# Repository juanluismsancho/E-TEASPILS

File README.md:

# E-TEASPILS
Teaching Environmental Awareness with Smart IoT Planters in Learning Spaces (TEASPILS)
Versión desarrollada por Juan Arquero, dentro del proyecto TEASPILS, Universidad Politécnica de Madrid

#TEASPIKE
Teaspike is a technological teaching tool that seechs to introduce students into IoT technoloy giving them the capability of monitoring planters installed in educational spaces.

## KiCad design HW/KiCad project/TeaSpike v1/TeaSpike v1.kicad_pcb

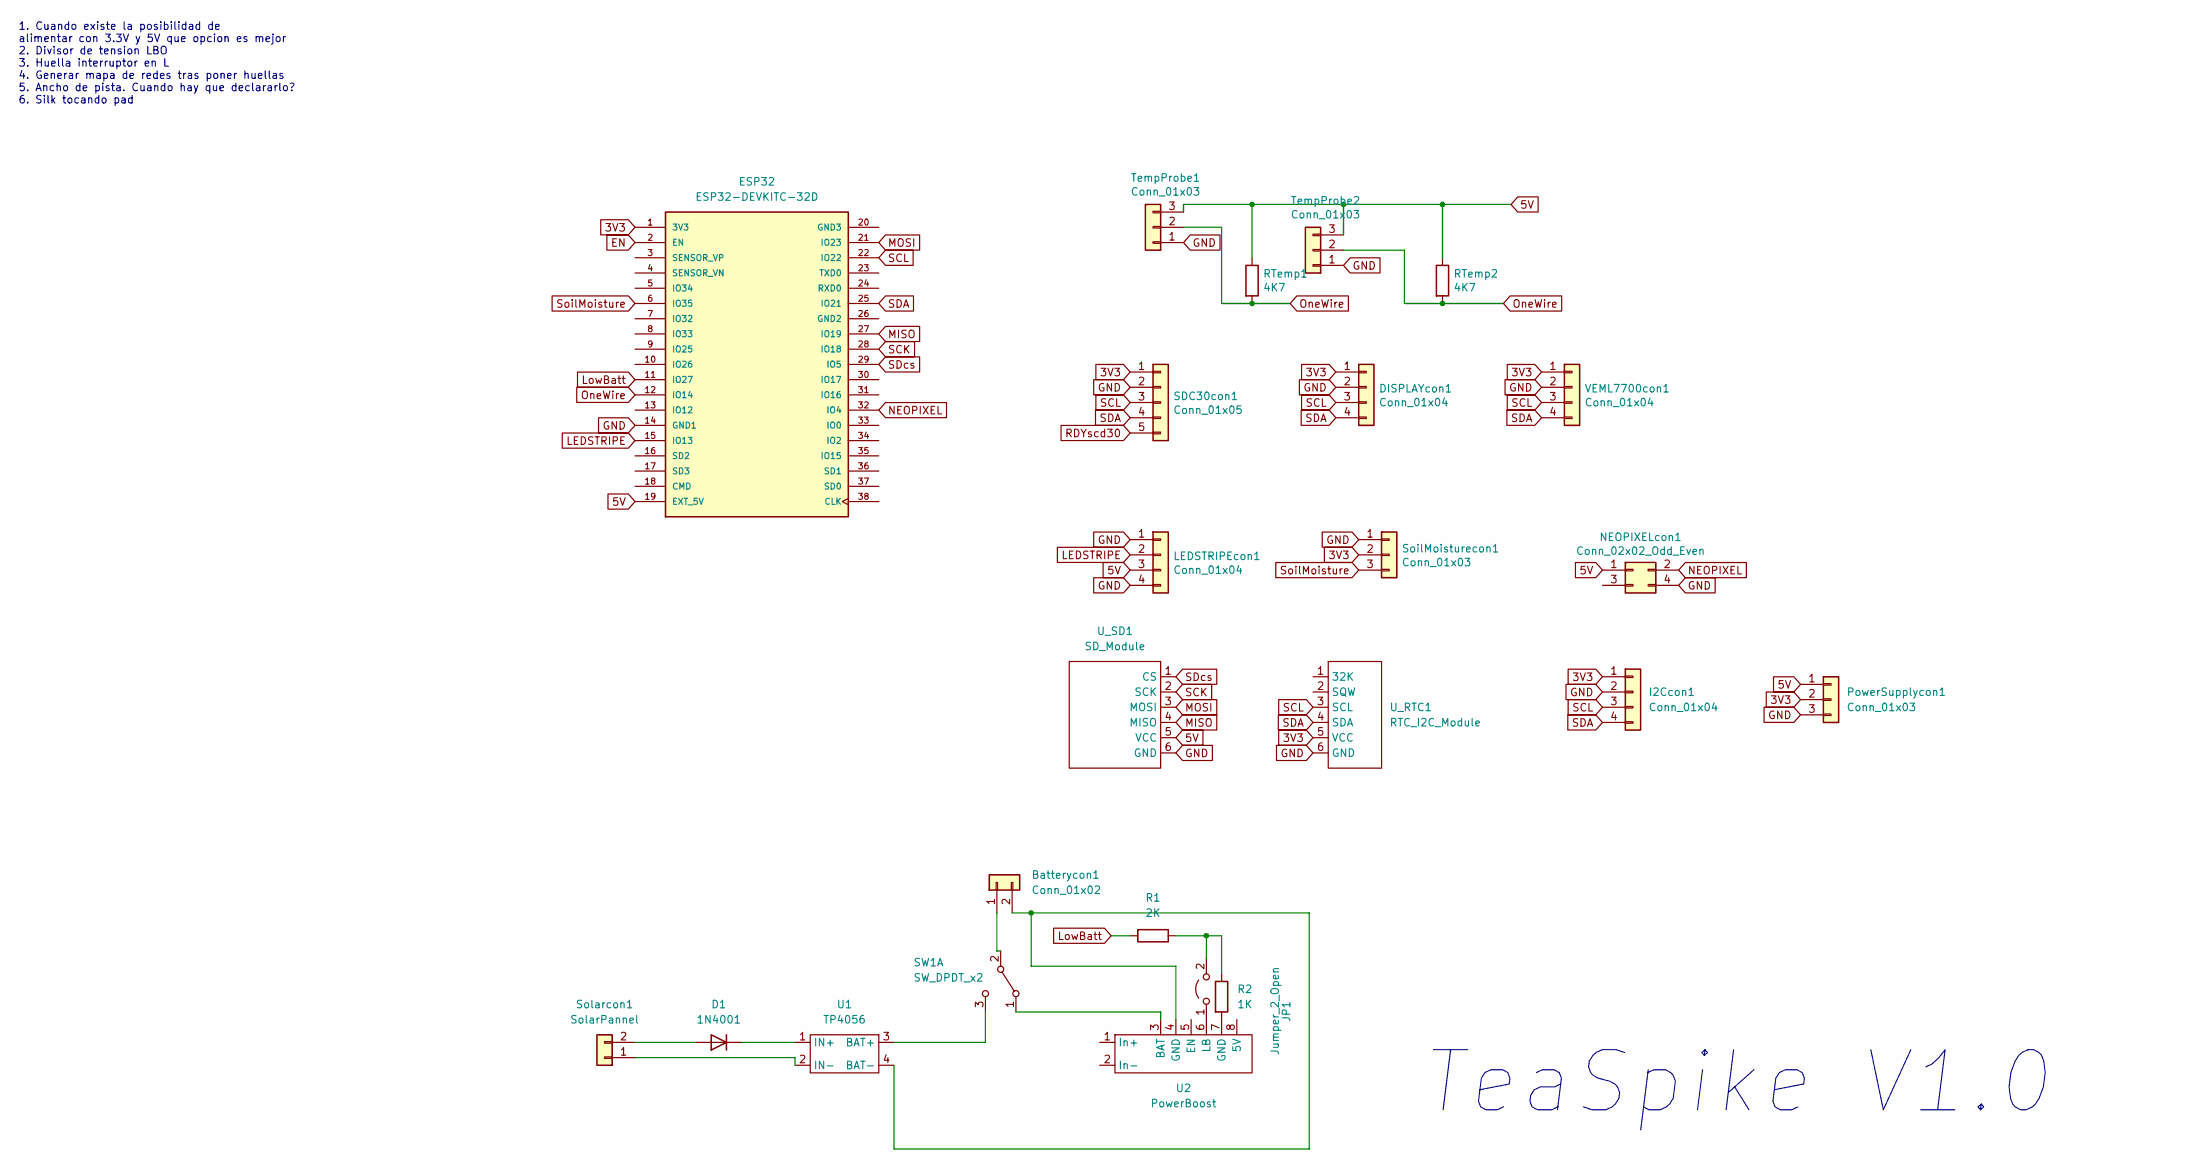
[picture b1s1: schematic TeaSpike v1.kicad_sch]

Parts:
Batterycon1: Conn_01x02; TerminalBlock_bornier-2_P5.08mm
D1: 1N4001; D_DO-41_SOD81_P10.16mm_Horizontal
DISPLAYcon1: Conn_01x04; JST_EH_B4B-EH-A_1x04_P2.50mm_Vertical
ESP32: ESP32-DEVKITC-32D; MODULE_ESP32-DEVKITC-32D; PARTREV 4
I2Ccon1: Conn_01x04; PinSocket_1x04_P2.54mm_Vertical
JP1: Jumper_2_Open; PinHeader_1x02_P2.54mm_Vertical
LEDSTRIPEcon1: Conn_01x04; JST_EH_B4B-EH-A_1x04_P2.50mm_Vertical
NEOPIXELcon1: Conn_02x02_Odd_Even; PinSocket_2x02_P2.54mm_Vertical
PowerSupplycon1: Conn_01x03; PinSocket_1x03_P2.54mm_Vertical
R1: 2K; R_Axial_DIN0207_L6.3mm_D2.5mm_P7.62mm_Horizontal
R2: 1K; R_Axial_DIN0207_L6.3mm_D2.5mm_P7.62mm_Horizontal
RTemp1, RTemp2: 4K7; R_Axial_DIN0207_L6.3mm_D2.5mm_P7.62mm_Horizontal
SDC30con1: Conn_01x05; JST_EH_B5B-EH-A_1x05_P2.50mm_Vertical
SW1: SW_DPDT_x2; SW_CuK_JS202011AQN_DPDT_Angled
SoilMoisturecon1: Conn_01x03; PinHeader_1x03_P2.54mm_Vertical
Solarcon1: SolarPannel; TerminalBlock_bornier-2_P5.08mm
TempProbe1, TempProbe2: Conn_01x03; JST_EH_B3B-EH-A_1x03_P2.50mm_Vertical
U1: TP4056
U2: PowerBoost
U_RTC1: RTC_I2C_Module
U_SD1: SD_Module
VEML7700con1: Conn_01x04; JST_EH_B4B-EH-A_1x04_P2.50mm_Vertical

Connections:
3V3: DISPLAYcon1.1, ESP32.1 (3V3), I2Ccon1.1, PowerSupplycon1.2, SDC30con1.1, SoilMoisturecon1.2, U_RTC1.5 (VCC), VEML7700con1.1
5V: ESP32.19 (EXT_5V), LEDSTRIPEcon1.3, NEOPIXELcon1.1, PowerSupplycon1.1, RTemp1.1, RTemp2.1, TempProbe1.3, TempProbe2.3, U_SD1.5 (VCC)
EN: ESP32.2 (EN)
GND: DISPLAYcon1.2, ESP32.14 (GND1), I2Ccon1.2, LEDSTRIPEcon1.1, LEDSTRIPEcon1.4, NEOPIXELcon1.4, PowerSupplycon1.3, SDC30con1.2, SoilMoisturecon1.1, TempProbe1.1, TempProbe2.1, U_RTC1.6 (GND), U_SD1.6 (GND), VEML7700con1.2
LEDSTRIPE: ESP32.15 (IO13), LEDSTRIPEcon1.2
LowBatt: ESP32.11 (IO27), R1.2
MISO: ESP32.27 (IO19), U_SD1.4 (MISO)
MOSI: ESP32.21 (IO23), U_SD1.3 (MOSI)
NEOPIXEL: ESP32.32 (IO4), NEOPIXELcon1.2
unnamed 9: Batterycon1.1, SW1.2 (B); also elsewhere on the board
unnamed: Batterycon1.2, U1.4 (BAT-), U2.4 (GND)
unnamed: D1.1 (K), U1.1 (IN+)
unnamed: D1.2 (A), Solarcon1.2
unnamed: JP1.1 (A), U2.6 (LB)
unnamed: JP1.2 (B), R1.1, R2.1
unnamed: R2.2, U2.7 (GND)
unnamed 16: SW1.1 (A), U2.3 (BAT); also elsewhere on the board
unnamed 17: SW1.3 (C), U1.3 (BAT+); also elsewhere on the board
unnamed: Solarcon1.1, U1.2 (IN-)
OneWire: ESP32.12 (IO14), RTemp1.2, RTemp2.2, TempProbe1.2, TempProbe2.2
RDYscd30: SDC30con1.5
SCK: ESP32.28 (IO18), U_SD1.2 (SCK)
SCL: DISPLAYcon1.3, ESP32.22 (IO22), I2Ccon1.3, SDC30con1.3, U_RTC1.3 (SCL), VEML7700con1.3
SDA: DISPLAYcon1.4, ESP32.25 (IO21), I2Ccon1.4, SDC30con1.4, U_RTC1.4 (SDA), VEML7700con1.4
SDcs: ESP32.29 (IO5), U_SD1.1 (CS)
SoilMoisture: ESP32.6 (IO35), SoilMoisturecon1.3

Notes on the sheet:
TeaSpike V1.0
1. Cuando existe la posibilidad de alimentar con 3.3V y 5V que opcion es mejor 2. Divisor de tension LBO 3. Huella interruptor en L 4. Generar mapa de redes tras poner huellas 5. Ancho de pista. Cuando hay que declararlo? 6. Silk tocando pad

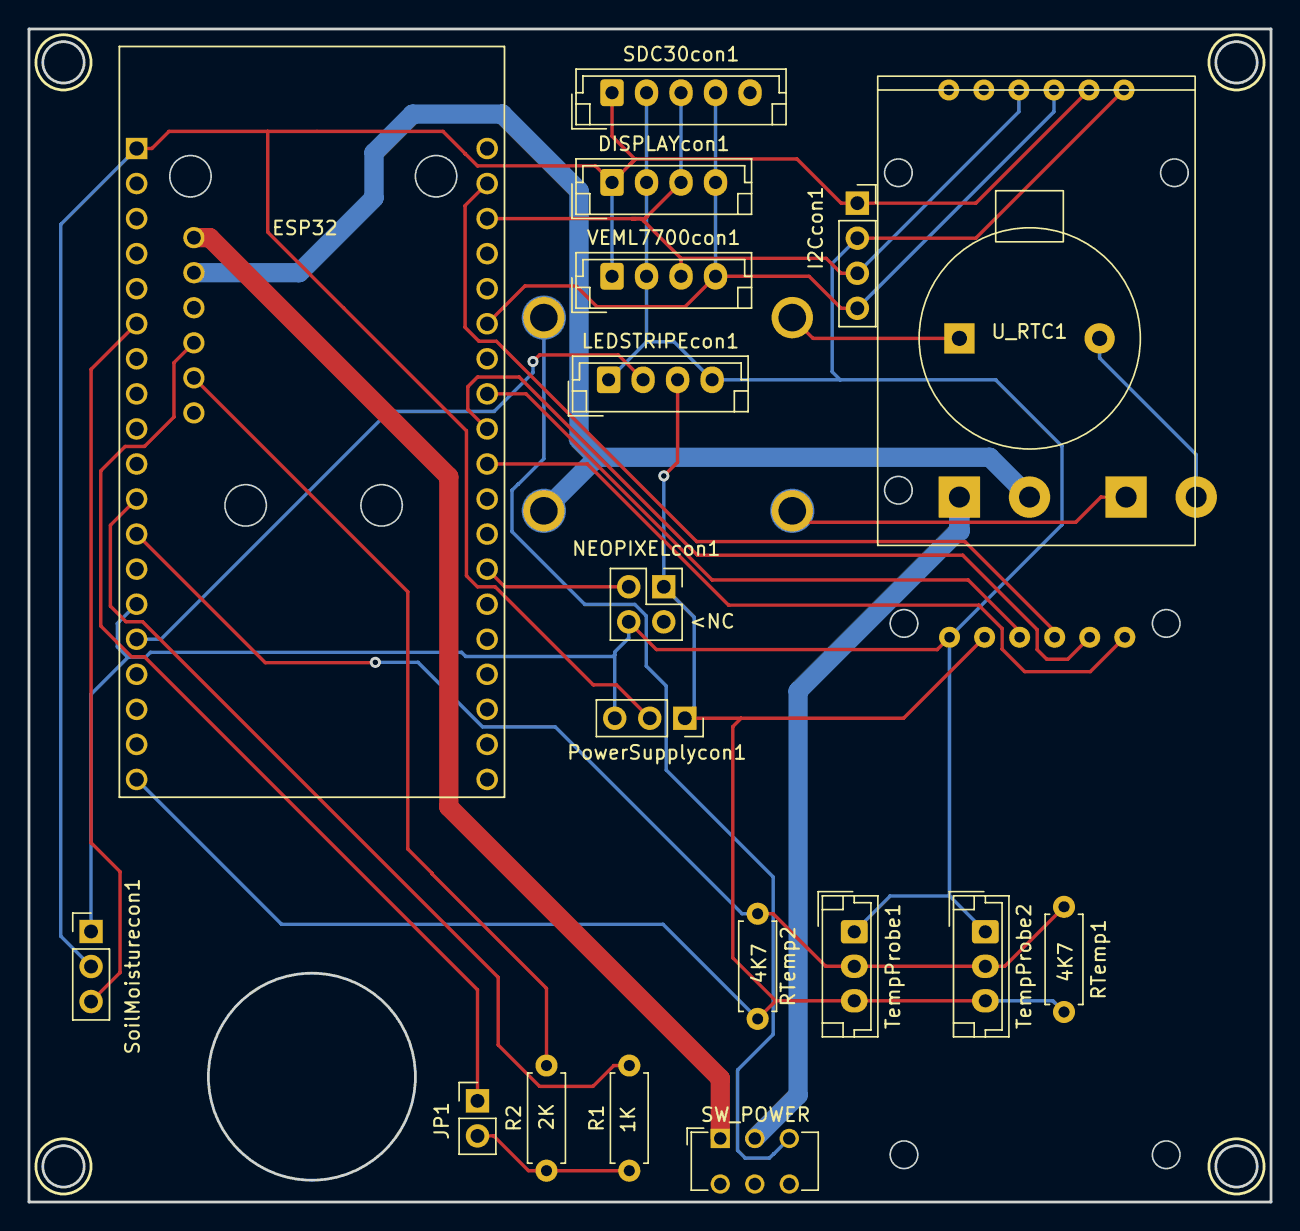
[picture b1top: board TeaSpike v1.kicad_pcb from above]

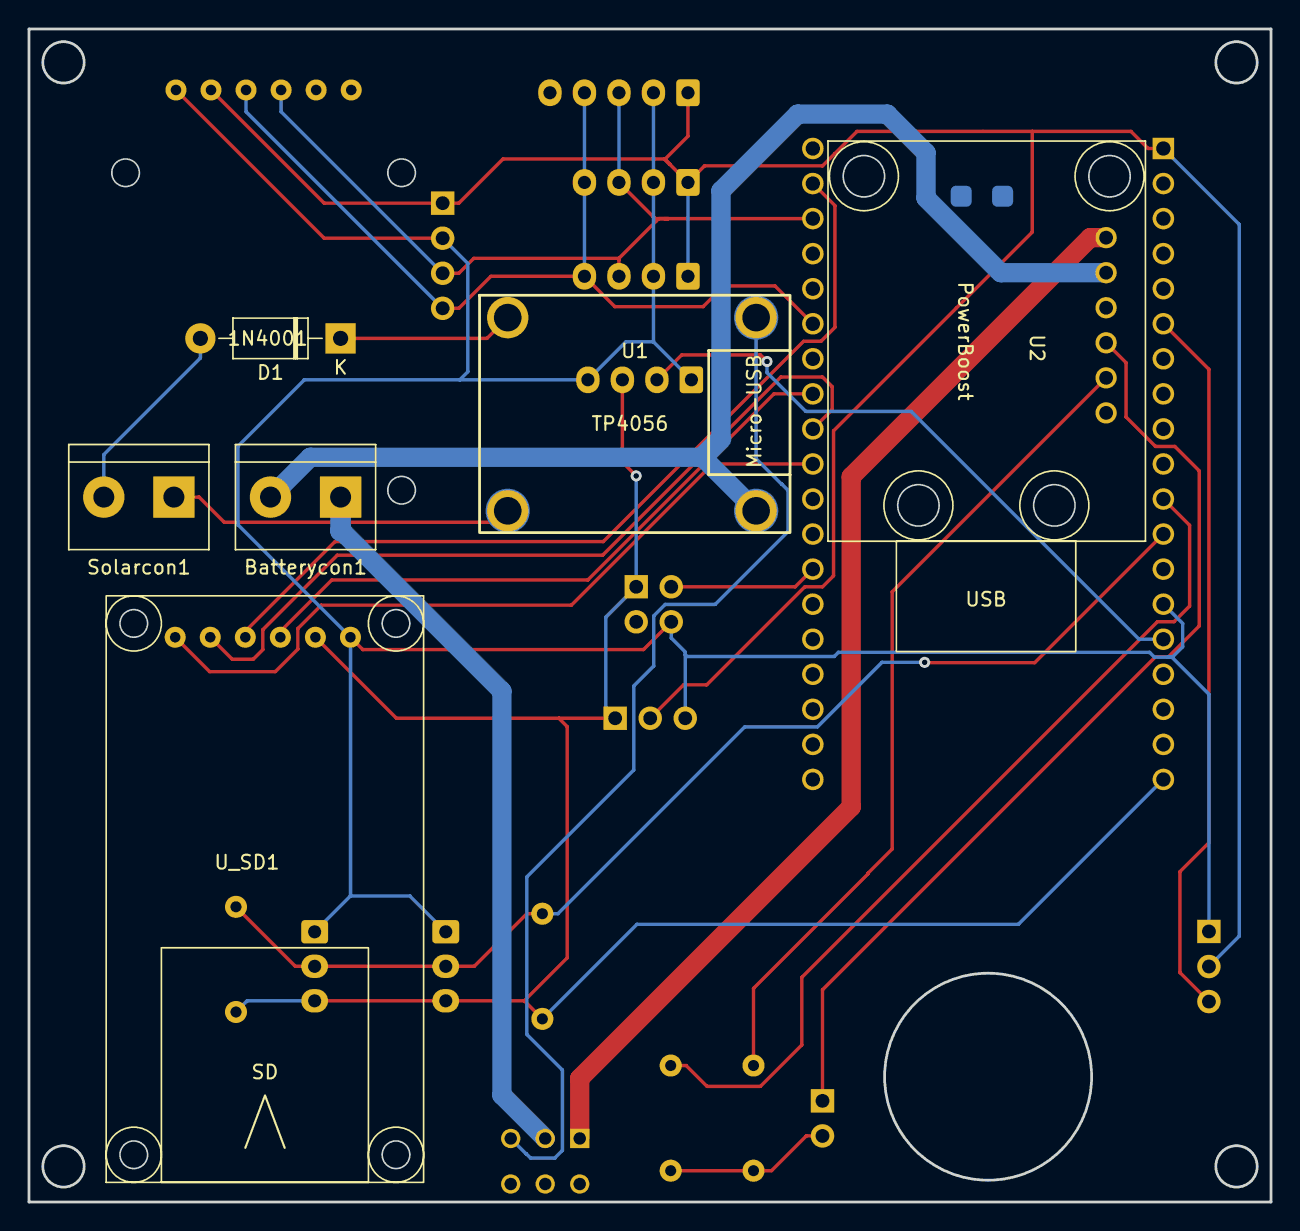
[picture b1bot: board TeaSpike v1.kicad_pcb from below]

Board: 2 copper layers, 90.0 x 85.0 mm, 24 parts (6 on the bottom side), 24 nets.

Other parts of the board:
SW_POWER: SW_DPDT_x2; SW_CuK_JS202011AQN_DPDT_Angled

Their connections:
unnamed 9: SW_POWER.2 (B); also elsewhere on the board
unnamed 16: SW_POWER.1 (A); also elsewhere on the board
unnamed 17: SW_POWER.3 (C); also elsewhere on the board

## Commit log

2021-01-31 Primera version sensores y IOT activo
2021-01-31 Se a optimizado la conexion a wifi y thingsboard
2021-01-31 Se ha añadido el guardado en una microSD externa
2021-02-02 Se añade esquema del sistema
2021-02-03 Se ha añadido reloj en tiempo real, luces errores y corregido bugs
2021-02-23 Rectificacion de codigo
2021-02-24 Update .gitignore
    Test
2021-02-27 added SD write and code reorganization
2021-03-02 Overview of initial arichtecture
2021-03-03 TEASPIL-APP added
2021-03-03 added TEASPIL-ESP32
2021-09-20 Create .gitignore
    Credentials should not be synched
2021-09-22 foto
2022-01-27 Ultima version
2022-02-20 Configuracion Workspace. Añando archivos de inicio
2022-02-20 Configuración Workspace. Añadida V1 y ficheros json de los dashboards de thingsboard.
2022-02-20 WORKSPACE CONFIGURADO CON ÉXITO
2022-02-21 Codigo reestructurado. A falta de corregir algunos errores (Quartile...)
2022-02-21 Corregidos errores. Añadida función para establecer mediante bot de telegram
2022-02-22 compare
2022-02-24 Actualizado gitignore para no incluir .zip de librerias
2022-02-24 Version funcional.
2022-02-25 Añadidas imagenes del modelo 3D
2022-02-25 añadidas imagenes
2022-02-25 Actualizado numero de LEDS en ring
2022-02-25 Version 2.0 depurada
2022-03-01 Añadidos datasets y funcion de simulacion
2022-03-02 Envio de datos a sever de UPF
2022-03-24 Added error code at the log prompted into SD card
2022-03-27 Excluido fichero de extensiones de vs code
2022-03-27 Añadido PIN Neopixel a configuracion
2022-03-28 Added first version of PCB. Currently developing
2022-03-29 Added footprints of periferalls
2022-03-31 Added second version of PCF after Norberto Cañas revision. Still developing
2022-03-31 Added SD-Module datasheet
2022-04-06 Corregida huella PowerBoost
2022-04-06 Reorganizado espacio de trabajo. Añadido analisis electrico
2022-04-06 Modificado circuito alimentación. Añadido aviso low bat.
2022-04-07 Versión tras revisión de Marina. Creado SpectraDSN. Falta routear las pistas
2022-04-07 Realizado routing
2022-04-07 Versión final para fabricación
2022-04-08 Corregido ancho de pista
2022-04-22 Versión fabricada
2022-04-27 Añadido pdf máscara
2022-05-29 Added Schematic in .pdf format and study of power consumption
2022-05-29 Updated gitignore
